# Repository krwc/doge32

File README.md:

# DOGE32 Features

## Small footprint

The board is 25mm x 59mm, which means it can fit into the standard breadboard nicely, and
each pin will be accessible.

## Battery slot

The board can be powered by 3.7V li-po battery.

## Low power consumption

In deep sleep mode, the board consumes only about 13µA. This is a pretty good result and will
let the device work for a long period of time on a battery.

## Dual supply support

You may power the device from battery as well as from the USB at the same time - useful feature
if you're making some quick fixes to the "already deployed" device.

## Built-in voltage measurement on IO35 pin

The IO35 pin of the ESP32 is connected to the (switchable via IO32), to avoid excessive current
draw input voltage divider, and can be used to determine the battery level of the battery.

## Cutting off the USB-UART converter when powered on from the battery

Many ESP32 boards don't do it, which is a problem, because [not all revisions of CP2102N enter
suspend state correctly](https://www.silabs.com/documents/public/errata/cp2102n-errata.pdf),
which means they draw current (a few milliamps) when they are not supposed to (e.g. when powered
on from the battery). This issue is fixed in our board.

## Slow rising reset fix

[ESP32 has a bug](https://www.esp32.com/viewtopic.php?t=5731) that makes automatic reset during
flashing with tools such as esptool.py not happening, and thus requires manual user intervention.

Our board also incorporates the fix for this problem.

# Renders

# Authors

Me and [dextero](https://github.com/dextero/). The board is an absolute overkill, built to monitor
soil moisture and eventually to help reminiding about watering plants more often ;-).

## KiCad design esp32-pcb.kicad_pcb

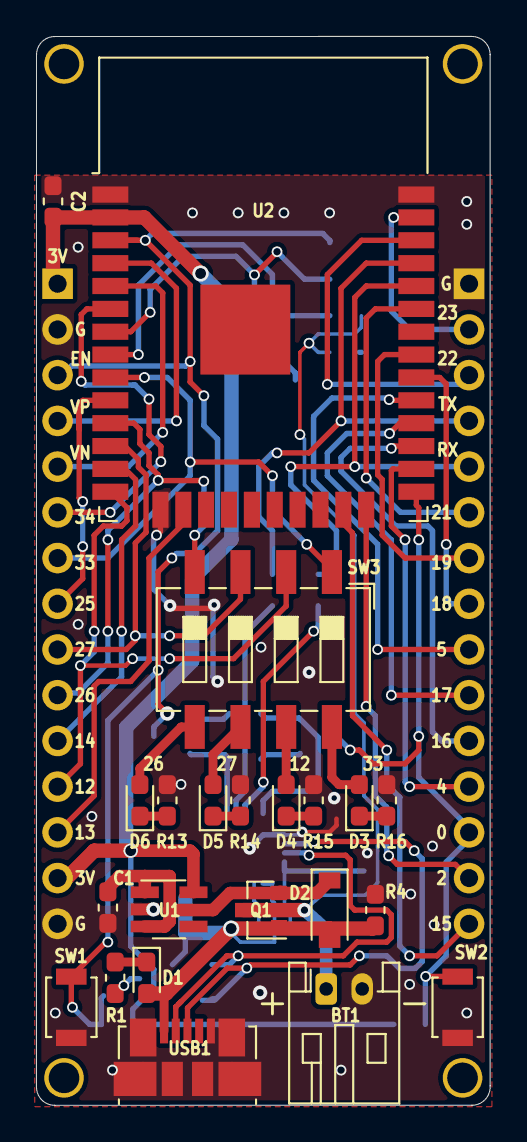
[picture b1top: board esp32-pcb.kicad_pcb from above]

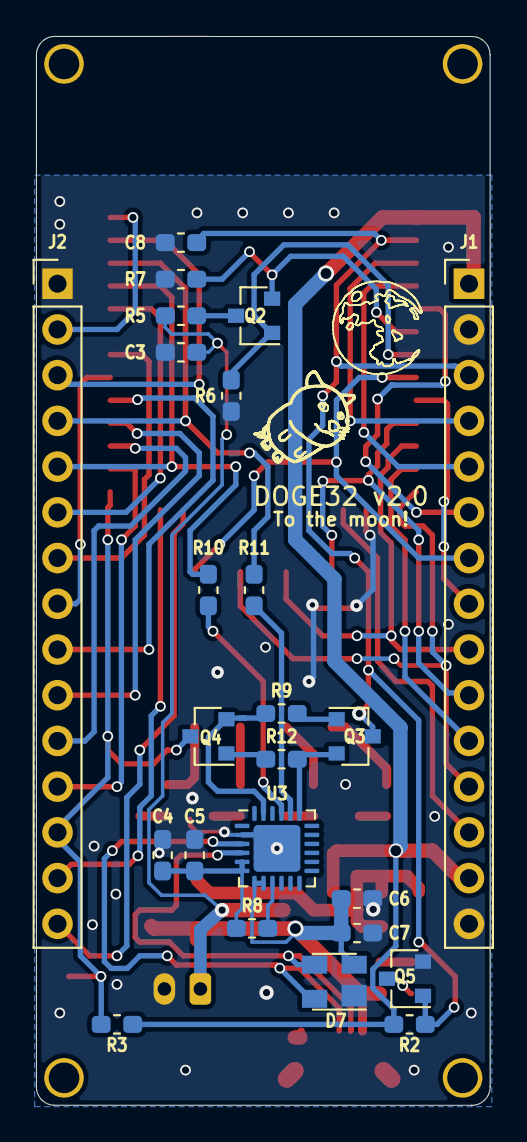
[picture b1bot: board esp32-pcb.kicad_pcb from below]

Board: 2 copper layers, 25.2 x 59.4 mm, 46 parts (24 on the bottom side), 53 nets.

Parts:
BT1: 3.7V; JST_PH_S2B-PH-K_1x02_P2.00mm_Horizontal
C1, C2: 10uF; C_0603_1608Metric_Pad1.05x0.95mm_HandSolder
C3, C5, C7: 0.1uF; C_0603_1608Metric_Pad1.05x0.95mm_HandSolder
C4, C6, C8: 4.7uF; C_0603_1608Metric_Pad1.05x0.95mm_HandSolder
D1: LED_USB_PWR; LED_0603_1608Metric_Pad1.05x0.95mm_HandSolder
D2: B140HW-7; D_SOD-123
D3: LED_RED; LED_0603_1608Metric_Pad1.05x0.95mm_HandSolder
D4: LED_GREEN; LED_0603_1608Metric_Pad1.05x0.95mm_HandSolder
D5: LED_BLUE; LED_0603_1608Metric_Pad1.05x0.95mm_HandSolder
D6: LED_YELLOW; LED_0603_1608Metric_Pad1.05x0.95mm_HandSolder
D7: SP0503BAHT; SOT-143
J1, J2: Conn_01x15_Male; PinHeader_1x15_P2.54mm_Vertical
Q1: SI2333DDS-T1-GE3; SOT-23
Q2, Q5: BSS138Q-7-F; SOT-23
Q3, Q4: MMBT3904; SOT-23
R1, R8, R10, R11: 1k; R_0603_1608Metric_Pad1.05x0.95mm_HandSolder
R2, R3, R4, R5, R6, R9, R12: 10k; R_0603_1608Metric_Pad1.05x0.95mm_HandSolder
R7: 30k; R_0603_1608Metric_Pad1.05x0.95mm_HandSolder
R13, R14, R15, R16: 470; R_0603_1608Metric_Pad1.05x0.95mm_HandSolder
SW1: RESET; SW_SPST_B3U-1000P
SW2: USER; SW_SPST_B3U-1000P
SW3: SW_DIP_x04; SW_DIP_SPSTx04_Slide_6.7x11.72mm_W8.61mm_P2.54mm_LowProfile
U1: XC6220B331MR; SOT-23-5_HandSoldering
U2: ESP32-WROOM-32
U3: CP2102N-A01-GQFN24; QFN-24-1EP_4x4mm_P0.5mm_EP2.6x2.6mm
USB1: MicroUSB type B; USB_Micro-B_Molex_47346-0001

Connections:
3V3: C2.2, J1.1, J1.14, R2.1, R3.2, U1.5, U2.2
5V_USB: C6.1, C7.1, D1.2, D2.2, D7.2, Q1.1, R4.2, U3.7, U3.8, USB1.1
EN: C8.1, J1.3, Q3.3, Q5.1, R2.2, SW1.2, U2.3
ESP_I34: J1.6, U2.6
ESP_IO0: J2.13, Q4.3, R3.1, SW2.1, U2.25
ESP_IO2: J2.14, U2.24
ESP_IO4: J2.12, U2.26
ESP_IO5: J2.9, U2.29
ESP_IO12: J1.12, SW3.2, U2.14
ESP_IO13: J1.13, U2.16
ESP_IO14: J1.11, U2.13
ESP_IO15: J2.15, U2.23
ESP_IO16: J2.11, U2.27
ESP_IO17: J2.10, U2.28
ESP_IO18: J2.8, U2.30
ESP_IO19: J2.7, U2.31
ESP_IO21: J2.6, U2.33
ESP_IO22: J2.3, U2.36
ESP_IO23: J2.2, U2.37
ESP_IO25: J1.8, U2.10
ESP_IO26: J1.10, SW3.4, U2.11
ESP_IO27: J1.9, SW3.3, U2.12
ESP_IO33: J1.7, SW3.1, U2.9
ESP_RXD0: J2.5, R10.2, U2.34
ESP_SENSOR_VN: J1.5, U2.5
ESP_SENSOR_VP: J1.4, U2.4
ESP_TXD0: J2.4, R11.2, U2.35
GND: BT1.2, C1.2, C2.1, C3.2, C4.2, C5.2, C6.2, C7.2, C8.2, D7.1, J1.2, J1.15, J2.1, Q5.2, R4.1, R6.1, R7.1, R13.2, R14.2, R15.2, R16.2, SW1.1, SW2.2, U1.2, U2.1, U2.15, U2.38, U3.2, U3.25, USB1.5, USB1.6
unnamed: C1.1, D2.1, Q1.2, U1.1, U1.3
unnamed: C4.1, C5.1, R8.2, U3.5, U3.6
unnamed: D1.1, R1.1
unnamed: D3.1, R16.1
unnamed: D3.2, SW3.8
unnamed: D4.1, R15.1
unnamed: D4.2, SW3.7
unnamed: D5.1, R14.1
unnamed: D5.2, SW3.6
unnamed: D6.1, R13.1
unnamed: D6.2, SW3.5
unnamed: Q2.3, R5.1
unnamed: Q3.1, R9.1
unnamed: Q3.2, R12.2, U3.19
unnamed: Q4.1, R12.1
unnamed: Q4.2, R9.2, U3.23
unnamed: Q5.3, R1.2
unnamed: R8.1, U3.9
unnamed: R10.1, U3.21
unnamed: R11.1, U3.20
USB_D+: D7.4, U3.3, USB1.3
USB_D-: D7.3, U3.4, USB1.2
V_BAT: BT1.1, C3.1, Q1.3, R5.2
V_BAT_HALF: Q2.2, R7.2, U2.7
V_BAT_MEASURE: Q2.1, R6.2, U2.8

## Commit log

2019-04-19 Add .gitignore
2019-04-19 Add initial project
2019-04-19 Add some stuff to .gitignore
2019-04-19 Added TSM2323CX to the local library
2019-04-19 Add battery protection circuit, switching between USB and VBAT.
2019-04-19 Update sym-lib-table
2019-04-20 Changed footprint of all low-power diodes to 0603 (1608m)
2019-04-20 Fix .gitignore: fp-info-cache is a file, not a directory.
2019-04-20 Changed LED footprints to 0603 (1608m)
2019-04-20 Changed resistors footprint to 0603 (1608m)
2019-04-20 Cosmetics: aligned V_IN label, changed R13 type to R_Small
2019-04-20 Changed footprint of a dip-switch to something more appropriate
2019-04-20 Changed footprints of buttons
2019-04-20 Changed capacitors footprints to 0603 (1608m)
2019-04-20 Moved input capacitor, so that +5V line is filtered as well. Added small cap on battery output.
2019-04-20 Changed filtering caps footprint. 10uF with 0603 footprint is not exactly easy to find.
2019-04-20 Changed footprint of S8050 transistors to SOT-23
2019-04-20 Use a 2.2k resistor after LED_USB_PWR to ground. Remove 3V3_USB label.
2019-04-20 Short J1_PIN2 directly to GND
2019-04-20 Short J1_PIN3 to ESP_EN, at the same time, move VP and VN to pins 4 and 5.
2019-04-20 Connect IO34 to J1_PIN6
2019-04-20 Connect VBAT directly to IO35
2019-04-20 Implement on-demand battery measurement circuit, providing half of battery voltage to measure.
2019-04-20 Replace BJTs with FETs
2019-04-20 Actually fix the circuit responsible for "auto programming"
2019-04-21 Revert using FETs for DTR and RTS switching. They are not as cheap as NPNs. Also, add a gate pulldown in battery measurement switch.
2019-04-21 Change footprint of 10uF capacitors once again to 0603.
2019-04-21 Modified CP2102N schematics to align with the old one
2019-04-21 Reworked USB-UART diagram: - added bypass capacitors for VBUS/REGIN and VIO/VDD as the datasheet suggests, - power is now delivered only from the USB port, - used regulated 3.3V VDD to bias VIO, - re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
2019-04-21 Make dipswitch 4-pin
2019-04-21 Reconnected every ESP32 pin following the order as in Figure 1 in ESP32-WROOM-32 datasheet
2019-04-26 Make layers visible again
2019-04-26 Created PCB layout. Used JST-PH 2mm connector.
2019-04-26 Label every goldpin, and align other labels so that they are readable
2019-04-26 Make battery power line 0.7mm
2019-04-26 Cleaned up tracks and vias
2019-04-26 Move doge to B.SilkS layer
2019-04-26 Updated to match final list of bought components
2019-04-26 Remove weird connection that did nothing
2019-04-26 Added even more vias and aligned them so that they do not interfere with graphics
2019-04-26 Added proper mounting holes
2019-04-26 Added mounting holes
2019-04-26 Made sure all components and their labels are by default visible
2019-04-26 Adapted replacement of DOGE to DOGE32
2019-04-26 Changed zones clearance to 0.25mm
2019-04-26 Added TVS protection
2019-04-26 Much pcb, very esp
2019-04-26 Do not place via on a pad if it is not necessary
2019-04-29 Increase 5V input trace width to 0.5mm
2019-05-05 Update PCB
2019-05-05 Add 4.7uF capacitor between EN and GND to ensure EN rising edge is slow
2019-05-05 Fix battery protection circuit by swapping terminals of p-MOS
2019-05-06 Use B140HW-7 Schottky diode instead of SD0805S020S1R0. The new diode has much lower guaranteed reverse current of 40µA rather than 0.2mA
2019-05-06 Use larger resistors for blue LEDs
2019-05-06 Turn off USB PWR led when the board is under reset
2019-05-06 Fix D2 text. Eliminate overlaps
2019-05-06 Connect D4 to IO12
2019-05-06 Label diodes with IO ports they are connected to
2019-05-06 Remove garbage D6 text hidden somewhere outside of the sheet
2019-05-13 Add clear battery polarization indicators to the silkscreen. Bump revision to v2.0
2019-05-15 Use 1k resistor instead of 2k for green PWR led
2019-05-15 Use XC6220B331MR
2019-05-15 Use 30k resistor for R7 so that 0.75 * VBAT is dropped at it instead of 0.5*VBAT. This should improve battery reading precision
2019-05-15 Move C1 a bit, so that the left corner GND and 3V labels are more visible
2019-05-30 Add initial README.md
2019-10-26 Mention small PCB footprint
